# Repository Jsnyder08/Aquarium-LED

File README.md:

# Aquarium-LED
Aquarium LED controller featuring esp8266 ds3231 at90usb1287 and color oled screen

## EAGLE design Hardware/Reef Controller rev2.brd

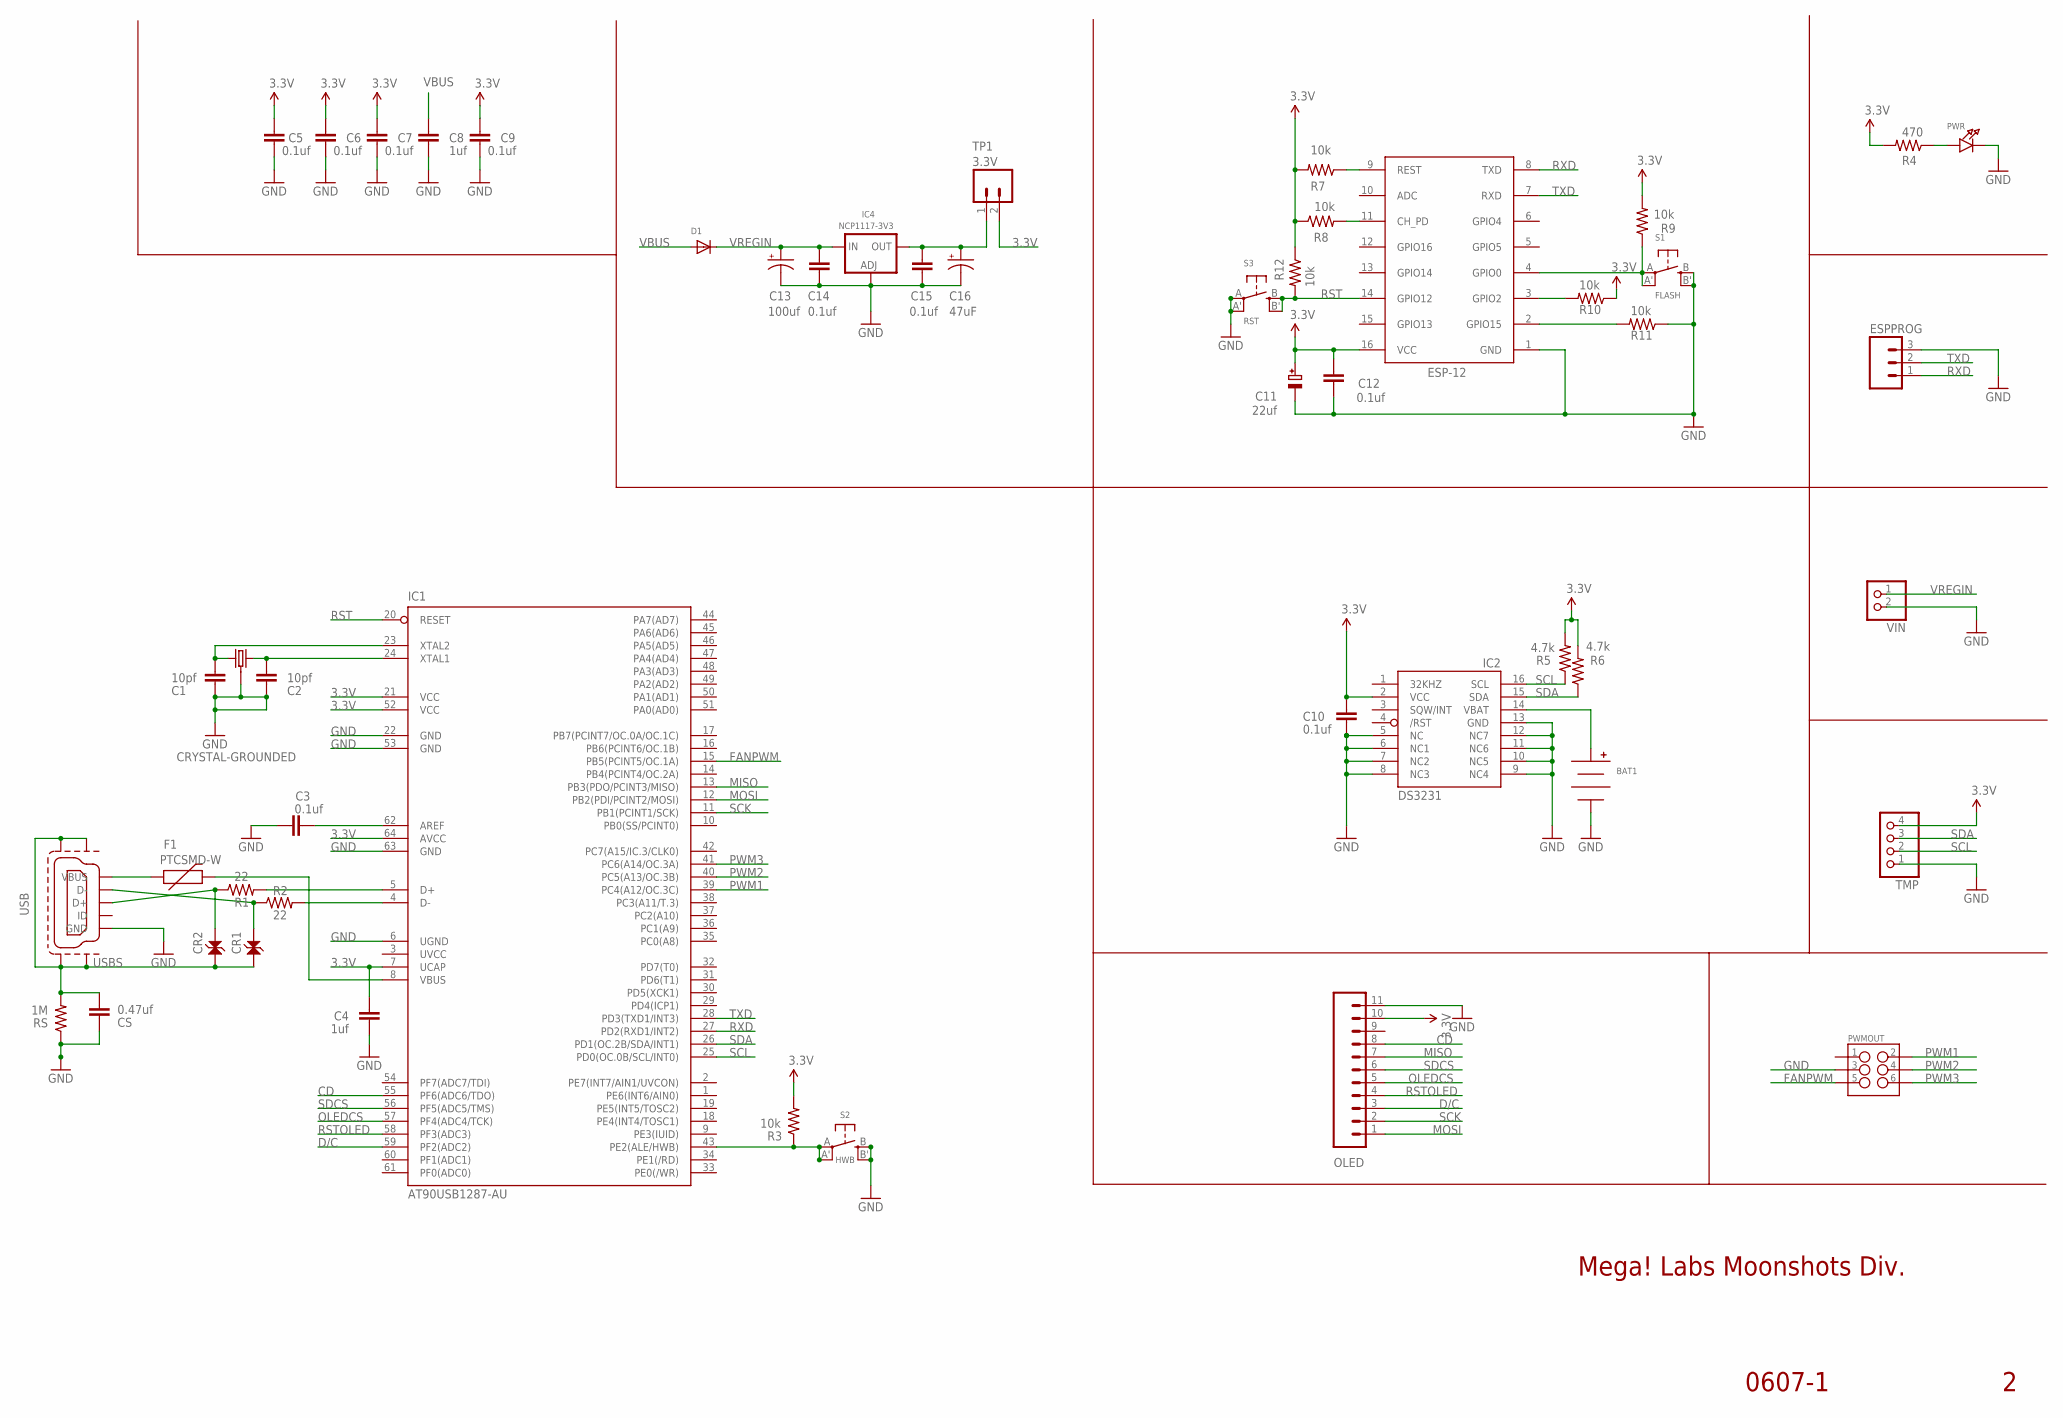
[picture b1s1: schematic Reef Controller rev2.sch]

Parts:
BAT1: BHX1-2032-SM
C1, C2: 10pf; 0805
C3, C5, C6, C7, C9, C10, C12, C14, C15: 0.1uf; 0805
C4, C8: 1uf; 0805
C11: 22uf; EIA3216-18/A-R
C13: 100uf; PANASONIC_D
C16: 47uF; EIA3528
CR1, CR2: PGB1010603
CS: 0.47uf; 0805
D1: DIODESOD-323F; SOD-323F
ESPPROG: M03PTH; 1X03
F1: PTCSMD-W; PTC-1206-WIDE
IC1: AT90USB1287-AU; TQFP64
IC2: DS3231/SO; SO16W
IC3: ESP-12
IC4: NCP1117-3V3; TO252
OLED: M11PTH; 1X11
PWMOUT: M03X2SHROUD; 2X3-SHROUDED
PWR: LED0805_NOOUTLINE; CHIPLED_0805_NOOUTLINE
R1, R2: 22; 0805
R3, R7, R8, R9, R10, R11, R12: 10k; 0805
R4: 470; 0805
R5, R6: 4.7k; 0805
RS: 1M; 0805
S1: FLASH; BTN_KMR2_4.6X2.8
S2: HWB; BTN_KMR2_4.6X2.8
S3: RST; BTN_KMR2_4.6X2.8
TMP: JST_4PIN; JSTPH4
TP1: 3.3V; 1X02
USB: MINI-USB-SHIELD-UX60-MB-5ST; UX60-MB-5ST
VIN: JST_2PIN-SMT-RA; JST-PH-2-SMT-RA
X1: CRYSTAL-GROUNDED; CRYSTAL-SMD-5X3

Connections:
3.3V: C4.2, C5.1, C6.1, C7.1, C9.1, C10.1, C11.+, C12.2, IC1.7 (UCAP), IC1.21 (VCC), IC1.52 (VCC), IC1.64 (AVCC), IC2.2 (VCC), IC3.16 (VCC), OLED.10, R3.2, R4.2, R5.2, R6.2, R7.2, R8.1, R9.2, R10.1, R12.1, TMP.4, TP1.2
CD: IC1.55 (PF6(ADC6/TDO)), OLED.8
D/C: IC1.59 (PF2(ADC2)), OLED.3
D_N: CR1.2, R2.1, USB.D-
D_N2: IC1.4 (D-), R2.2
D_P: CR2.2, R1.1, USB.D+
D_P2: IC1.5 (D+), R1.2
FANPWM: IC1.15 (PB5(PCINT5/OC.1A)), PWMOUT.5
GND: BAT1.2 (NEG), C1.2, C2.2, C3.1, C4.1, C5.2, C6.2, C7.2, C8.2, C9.2, C10.2, C11.-, C12.1, C13.-, C14.2, C15.2, C16.C (-), CS.1, ESPPROG.3, IC1.6 (UGND), IC1.22 (GND), IC1.53 (GND), IC1.63 (GND), IC2.5 (NC), IC2.6 (NC1), IC2.7 (NC2), IC2.8 (NC3), IC2.9 (NC4), IC2.10 (NC5), IC2.11 (NC6), IC2.12 (NC7), IC2.13 (GND), IC3.1 (GND), IC4.1 (ADJ), OLED.11, PWMOUT.3, PWR.C, R11.1, RS.1, S1.B (S), S1.B' (S1), S2.B (S), S2.B' (S1), S3.A, S3.A' (P1), TMP.1, USB.GND, VIN.2 (1), X1.2 (3), X1.4 (3)
MISO: IC1.13 (PB3(PDO/PCINT3/MISO)), OLED.7
MOSI: IC1.12 (PB2(PDI/PCINT2/MOSI)), OLED.1
unnamed: IC1.43 (PE2(ALE/HWB)), R3.1, S2.A, S2.A' (P1)
unnamed: IC3.3 (GPIO2), R10.2
unnamed: IC3.4 (GPIO0), R9.1, S1.A, S1.A' (P1)
unnamed: CR1.1, CR2.1, CS.2, RS.2, USB.M1 (M3), USB.M2, USB.M3 (M4), USB.M4 (M1)
unnamed: PWR.A, R4.1
unnamed: BAT1.1 (POS), IC2.14 (VBAT)
unnamed: C3.2, IC1.62 (AREF)
unnamed: IC3.11 (CH_PD), R8.2
unnamed: F1.1, USB.VBUS
unnamed: IC3.2 (GPIO15), R11.2
unnamed: IC3.9 (REST), R7.1
unnamed: C15.1, C16.A (+), IC4.3 (OUT), TP1.1
OLEDCS: IC1.57 (PF4(ADC4/TCK)), OLED.5
PWM1: IC1.39 (PC4(A12/OC.3C)), PWMOUT.2
PWM2: IC1.40 (PC5(A13/OC.3B)), PWMOUT.4
PWM3: IC1.41 (PC6(A14/OC.3A)), PWMOUT.6
RST: IC1.20 (RESET), IC3.14 (GPIO12), R12.2, S3.B (S), S3.B' (S1)
RSTOLED: IC1.58 (PF3(ADC3)), OLED.4
RXD: ESPPROG.1, IC1.27 (PD2(RXD1/INT2)), IC3.8 (TXD)
SCK: IC1.11 (PB1(PCINT1/SCK)), OLED.2
SCL: IC1.25 (PD0(OC.0B/SCL/INT0)), IC2.16 (SCL), R5.1, TMP.2
SDA: IC1.26 (PD1(OC.2B/SDA/INT1)), IC2.15 (SDA), R6.1, TMP.3
SDCS: IC1.56 (PF5(ADC5/TMS)), OLED.6
TXD: ESPPROG.2, IC1.28 (PD3(TXD1/INT3)), IC3.7 (RXD)
UVCC: IC1.3 (UVCC)
VBUS: C8.1, D1.A, F1.2, IC1.8 (VBUS)
VREGIN: C13.+, C14.1, D1.C, IC4.2 (IN), VIN.1 (2)
XTAL_N: C1.1, IC1.23 (XTAL2), X1.3 (1)
XTAL_P: C2.1, IC1.24 (XTAL1), X1.1 (2)

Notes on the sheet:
Mega! Labs Moonshots Div.
0607-1

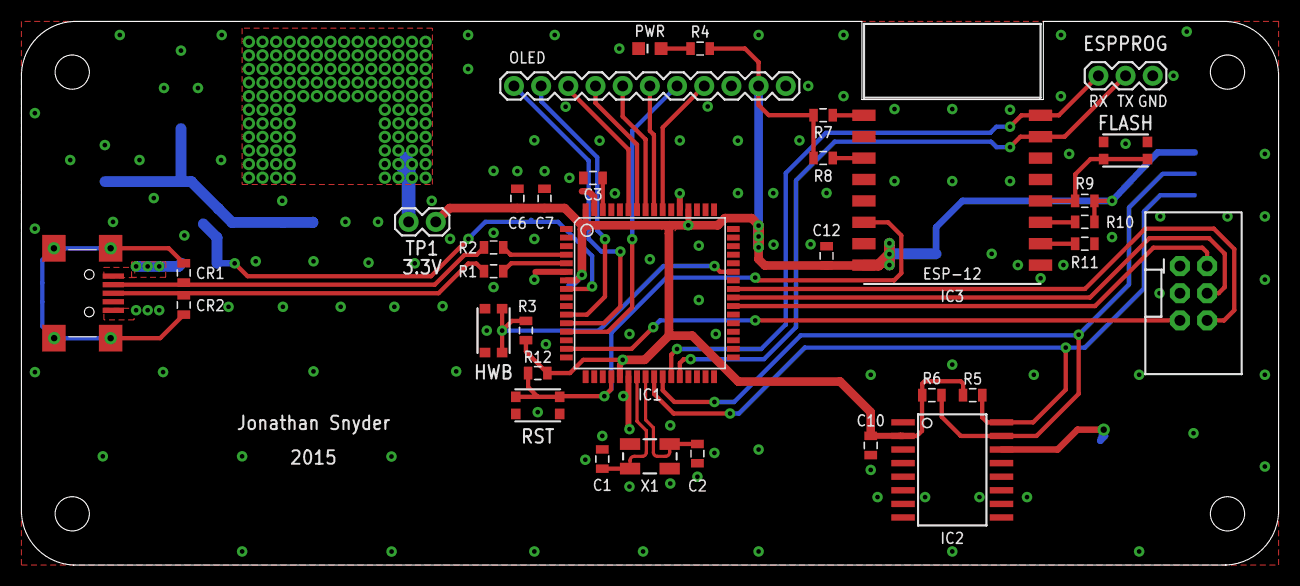
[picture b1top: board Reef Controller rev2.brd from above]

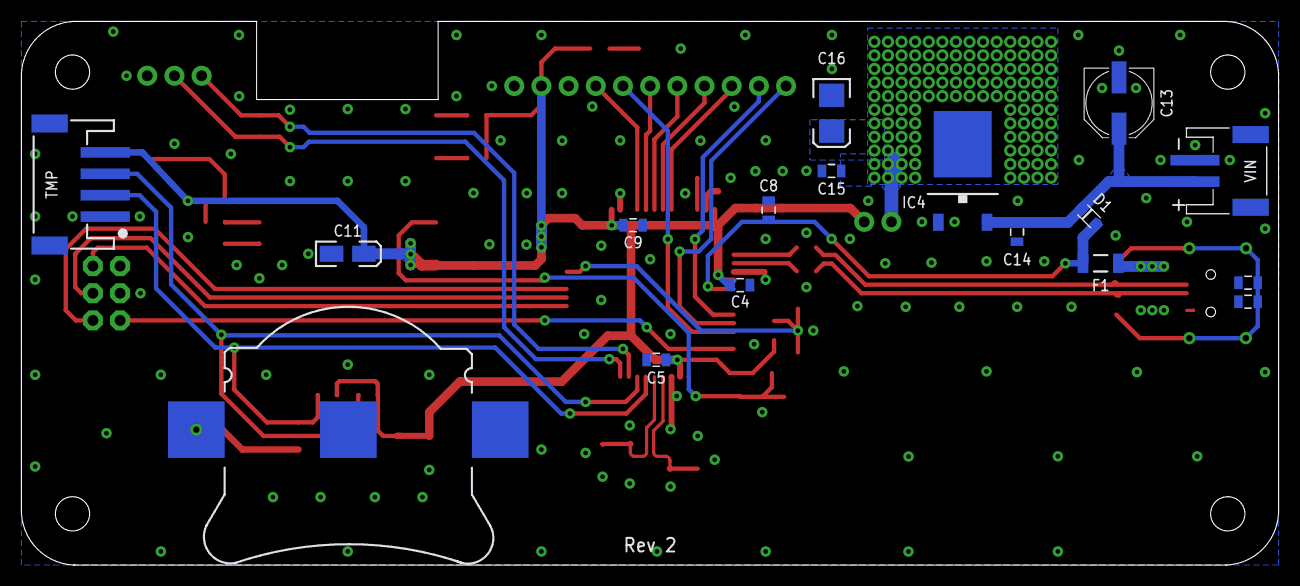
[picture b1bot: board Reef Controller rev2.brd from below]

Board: 2 copper layers, 117.5 x 50.8 mm, 52 parts (17 on the bottom side), 39 nets.

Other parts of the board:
U$1: OSHW-LOGO-L_COPPER

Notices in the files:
parts and their libraries:
microbuilder: This work is placed in the public domain, and may be freely used for commercial and non-commercial work with the following conditions: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
SparkFun-Passives: Licensing: Creative Commons ShareAlike 4.0 International - https://creativecommons.org/licenses/by-sa/4.0
